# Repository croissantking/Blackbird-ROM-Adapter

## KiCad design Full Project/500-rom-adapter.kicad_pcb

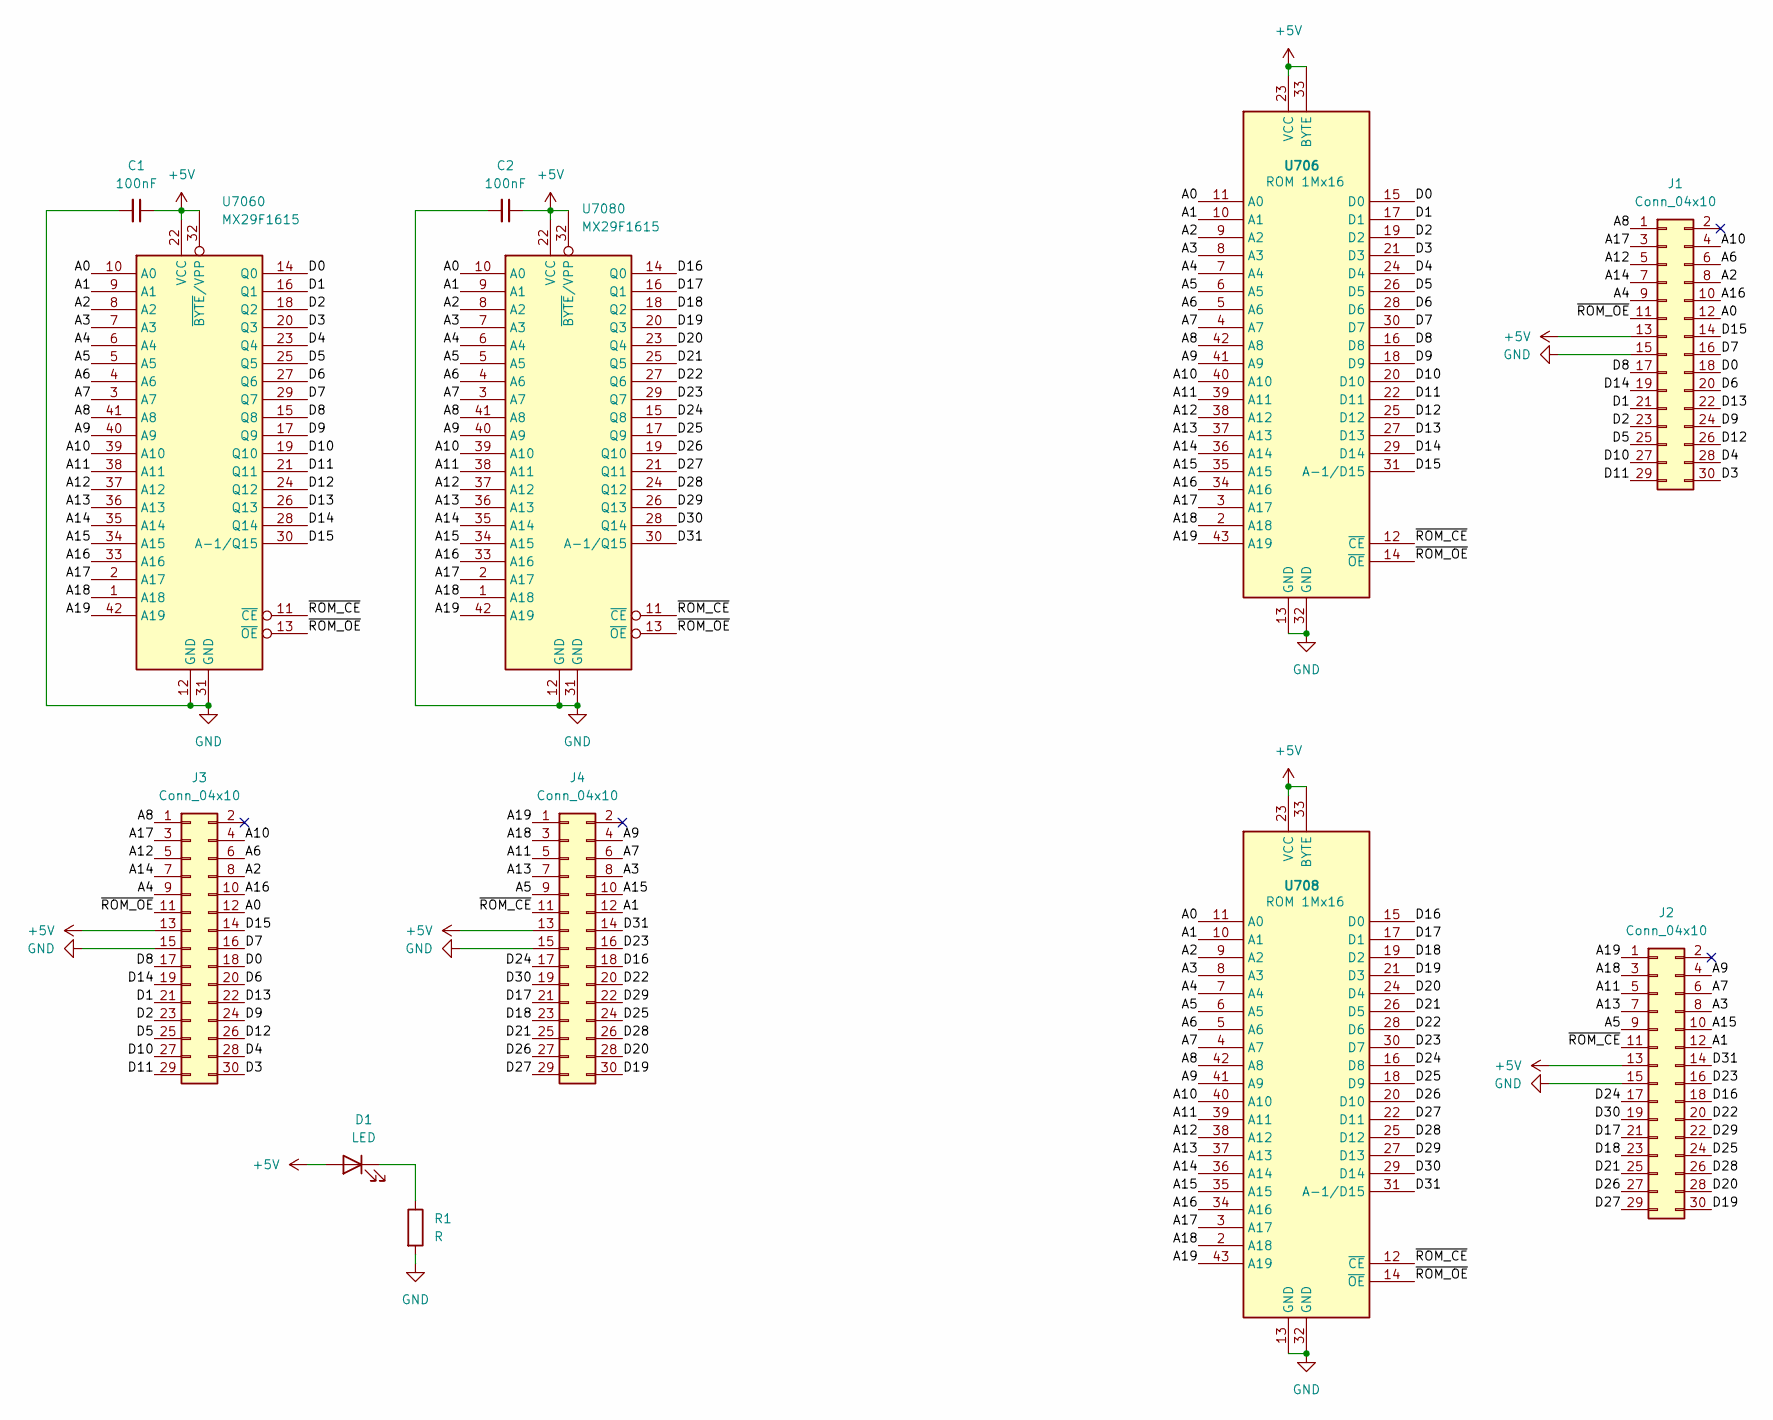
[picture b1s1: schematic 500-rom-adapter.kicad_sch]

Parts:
C1, C2: 100nF; C_0805_2012Metric_Pad1.18x1.45mm_HandSolder
D1: LED; LED_0805_2012Metric
J1, J2, J3, J4: Conn_04x10; PinSocket_3x10_P2.00mm_Vertical_PB500
R1: R; R_0805_2012Metric_Pad1.20x1.40mm_HandSolder
U706, U708: ROM 1Mx16; SOP-44_12.6_CASTELLATED
U7060, U7080: MX29F1615; DIP-42_W15.24mm_Socket_LongPads

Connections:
+5V: C1.1, C2.1, D1.2 (A), J1.13, J2.13, J3.13, J4.13, U706.23 (VCC), U706.33 (BYTE), U708.23 (VCC), U708.33 (BYTE), U7060.22 (VCC), U7060.32 (~BYTE/VPP), U7080.22 (VCC), U7080.32 (~BYTE/VPP); also elsewhere on the board
/A0: J1.12, J3.12, U706.11 (A0), U708.11 (A0), U7060.10 (A0), U7080.10 (A0)
/A1: J2.12, J4.12, U706.10 (A1), U708.10 (A1), U7060.9 (A1), U7080.9 (A1)
/A2: J1.8, J3.8, U706.9 (A2), U708.9 (A2), U7060.8 (A2), U7080.8 (A2)
/A3: J2.8, J4.8, U706.8 (A3), U708.8 (A3), U7060.7 (A3), U7080.7 (A3)
/A4: J1.9, J3.9, U706.7 (A4), U708.7 (A4), U7060.6 (A4), U7080.6 (A4)
/A5: J2.9, J4.9, U706.6 (A5), U708.6 (A5), U7060.5 (A5), U7080.5 (A5)
/A6: J1.6, J3.6, U706.5 (A6), U708.5 (A6), U7060.4 (A6), U7080.4 (A6)
/A7: J2.6, J4.6, U706.4 (A7), U708.4 (A7), U7060.3 (A7), U7080.3 (A7)
/A8: J1.1, J3.1, U706.42 (A8), U708.42 (A8), U7060.41 (A8), U7080.41 (A8)
/A9: J2.4, J4.4, U706.41 (A9), U708.41 (A9), U7060.40 (A9), U7080.40 (A9)
/A10: J1.4, J3.4, U706.40 (A10), U708.40 (A10), U7060.39 (A10), U7080.39 (A10)
/A11: J2.5, J4.5, U706.39 (A11), U708.39 (A11), U7060.38 (A11), U7080.38 (A11)
/A12: J1.5, J3.5, U706.38 (A12), U708.38 (A12), U7060.37 (A12), U7080.37 (A12)
/A13: J2.7, J4.7, U706.37 (A13), U708.37 (A13), U7060.36 (A13), U7080.36 (A13)
/A14: J1.7, J3.7, U706.36 (A14), U708.36 (A14), U7060.35 (A14), U7080.35 (A14)
/A15: J2.10, J4.10, U706.35 (A15), U708.35 (A15), U7060.34 (A15), U7080.34 (A15)
/A16: J1.10, J3.10, U706.34 (A16), U708.34 (A16), U7060.33 (A16), U7080.33 (A16)
/A17: J1.3, J3.3, U706.3 (A17), U708.3 (A17), U7060.2 (A17), U7080.2 (A17)
/A18: J2.3, J4.3, U706.2 (A18), U708.2 (A18), U7060.1 (A18), U7080.1 (A18)
/A19: J2.1, J4.1, U706.43 (A19), U708.43 (A19), U7060.42 (A19), U7080.42 (A19)
/D0: J1.18, J3.18, U706.15 (D0), U7060.14 (Q0)
/D1: J1.21, J3.21, U706.17 (D1), U7060.16 (Q1)
/D2: J1.23, J3.23, U706.19 (D2), U7060.18 (Q2)
/D3: J1.30, J3.30, U706.21 (D3), U7060.20 (Q3)
/D4: J1.28, J3.28, U706.24 (D4), U7060.23 (Q4)
/D5: J1.25, J3.25, U706.26 (D5), U7060.25 (Q5)
/D6: J1.20, J3.20, U706.28 (D6), U7060.27 (Q6)
/D7: J1.16, J3.16, U706.30 (D7), U7060.29 (Q7)
/D8: J1.17, J3.17, U706.16 (D8), U7060.15 (Q8)
/D9: J1.24, J3.24, U706.18 (D9), U7060.17 (Q9)
/D10: J1.27, J3.27, U706.20 (D10), U7060.19 (Q10)
/D11: J1.29, J3.29, U706.22 (D11), U7060.21 (Q11)
/D12: J1.26, J3.26, U706.25 (D12), U7060.24 (Q12)
/D13: J1.22, J3.22, U706.27 (D13), U7060.26 (Q13)
/D14: J1.19, J3.19, U706.29 (D14), U7060.28 (Q14)
/D15: J1.14, J3.14, U706.31 (A-1/D15), U7060.30 (A-1/Q15)
/D16: J2.18, J4.18, U708.15 (D0), U7080.14 (Q0)
/D17: J2.21, J4.21, U708.17 (D1), U7080.16 (Q1)
/D18: J2.23, J4.23, U708.19 (D2), U7080.18 (Q2)
/D19: J2.30, J4.30, U708.21 (D3), U7080.20 (Q3)
/D20: J2.28, J4.28, U708.24 (D4), U7080.23 (Q4)
/D21: J2.25, J4.25, U708.26 (D5), U7080.25 (Q5)
/D22: J2.20, J4.20, U708.28 (D6), U7080.27 (Q6)
/D23: J2.16, J4.16, U708.30 (D7), U7080.29 (Q7)
/D24: J2.17, J4.17, U708.16 (D8), U7080.15 (Q8)
/D25: J2.24, J4.24, U708.18 (D9), U7080.17 (Q9)
/D26: J2.27, J4.27, U708.20 (D10), U7080.19 (Q10)
/D27: J2.29, J4.29, U708.22 (D11), U7080.21 (Q11)
/D28: J2.26, J4.26, U708.25 (D12), U7080.24 (Q12)
/D29: J2.22, J4.22, U708.27 (D13), U7080.26 (Q13)
/D30: J2.19, J4.19, U708.29 (D14), U7080.28 (Q14)
/D31: J2.14, J4.14, U708.31 (A-1/D15), U7080.30 (A-1/Q15)
/~ROM_CE: J2.11, J4.11, U706.12 (~CE), U708.12 (~CE), U7060.11 (~CE), U7080.11 (~CE)
/~ROM_OE: J1.11, J3.11, U706.14 (~OE), U708.14 (~OE), U7060.13 (~OE), U7080.13 (~OE)
GND: C1.2, C2.2, J1.15, J2.15, J3.15, J4.15, R1.2, U706.13 (GND), U706.32 (GND), U708.13 (GND), U708.32 (GND), U7060.12 (GND), U7060.31 (GND), U7080.12 (GND), U7080.31 (GND)
unnamed 56: D1.1 (K), R1.1; also elsewhere on the board

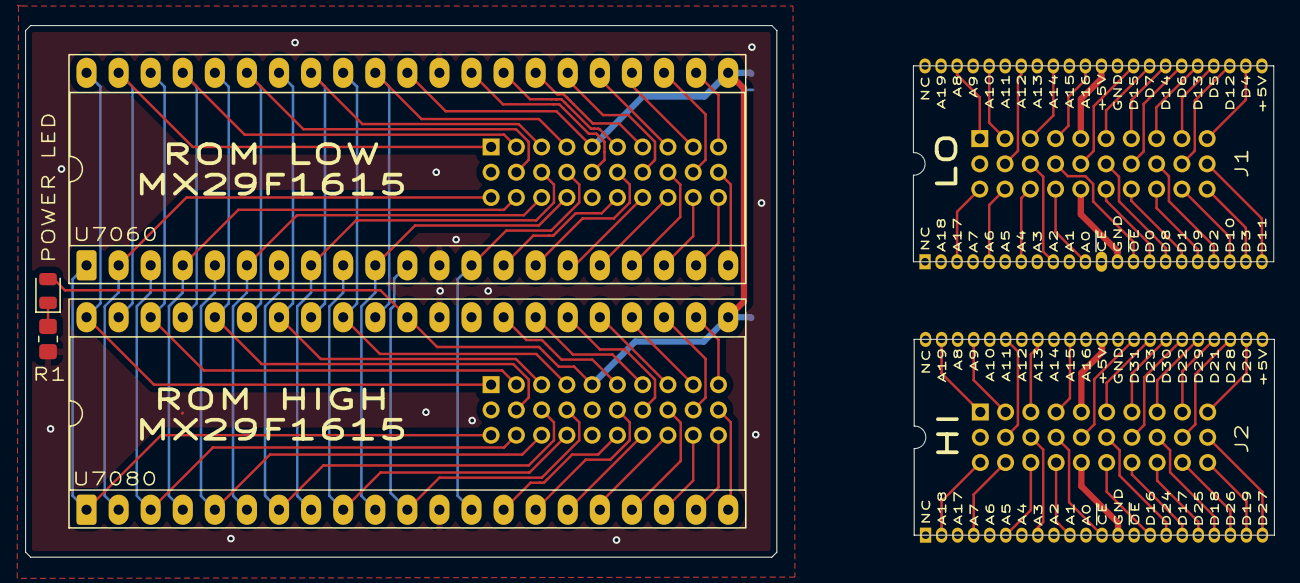
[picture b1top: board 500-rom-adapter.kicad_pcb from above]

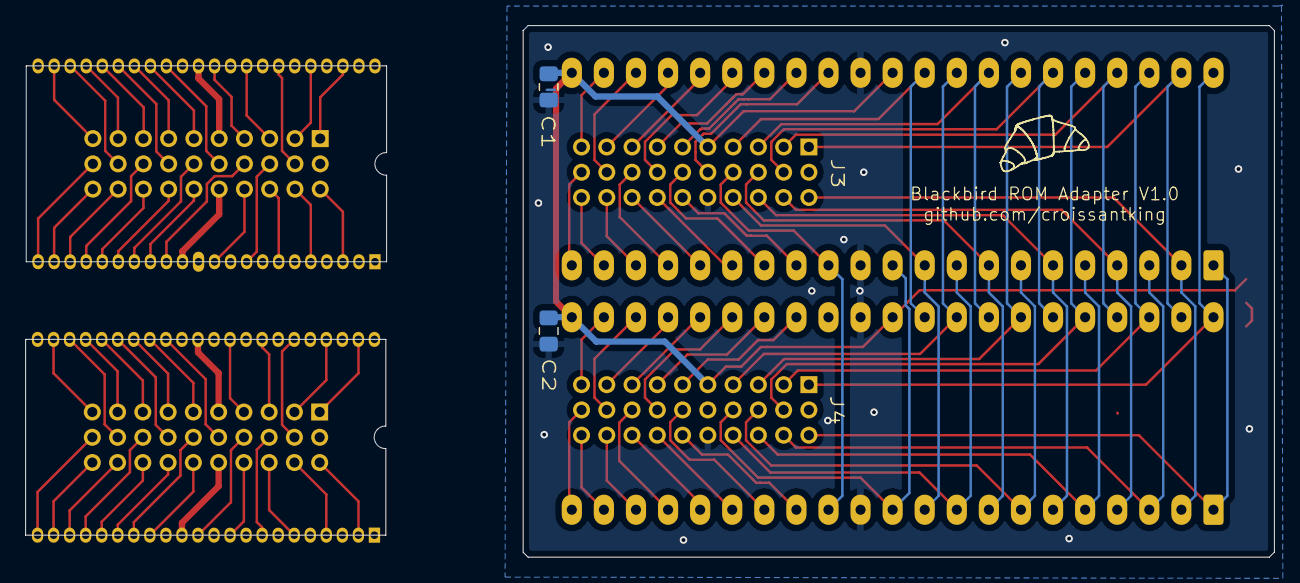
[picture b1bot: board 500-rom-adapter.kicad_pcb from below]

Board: 2 copper layers, 98.9 x 42.1 mm, 12 parts (2 on the bottom side), 57 nets.

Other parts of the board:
POWER LED: LED; LED_0805_2012Metric

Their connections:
+5V: POWER LED.2 (A); also elsewhere on the board
unnamed 56: POWER LED.1 (K); also elsewhere on the board

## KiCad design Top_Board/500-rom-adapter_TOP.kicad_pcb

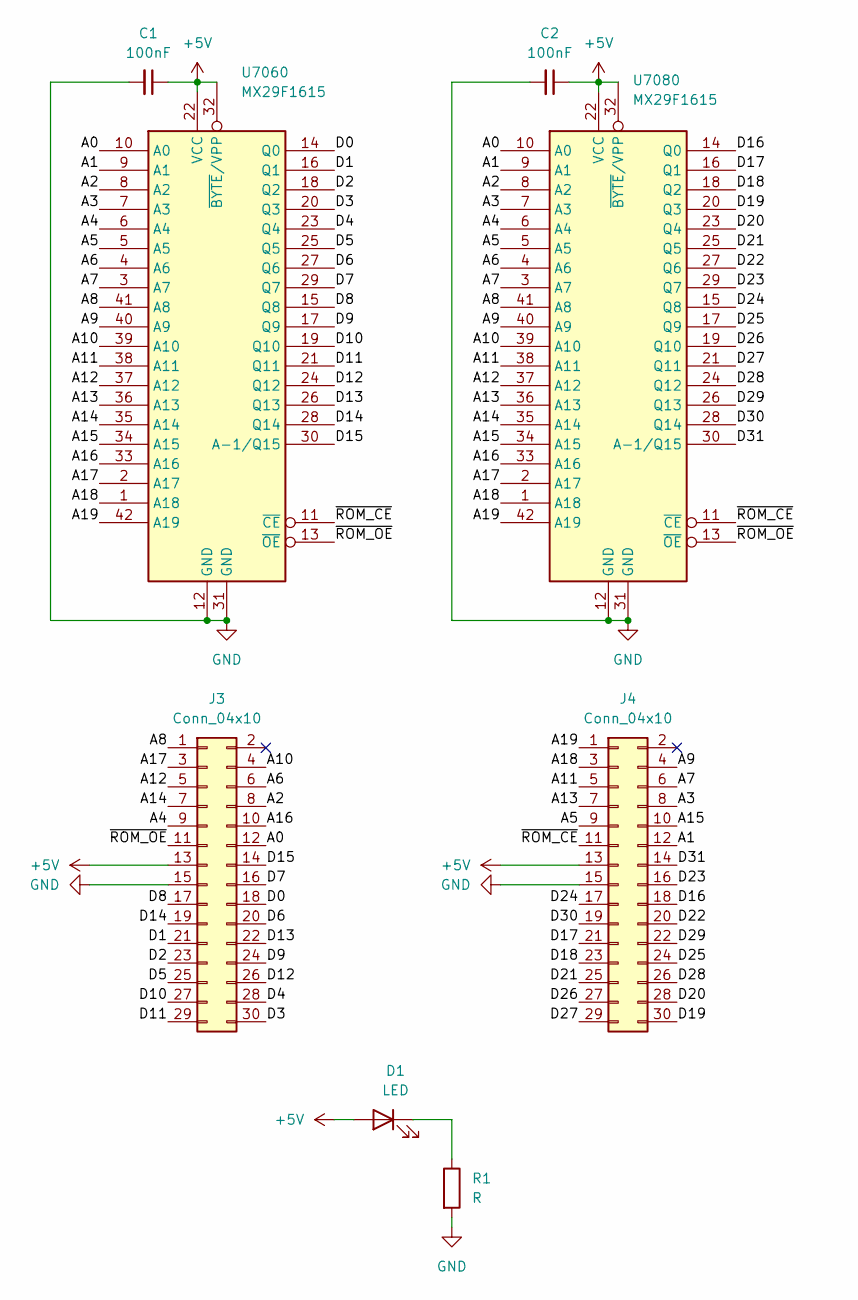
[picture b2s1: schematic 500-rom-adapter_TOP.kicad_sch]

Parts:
C1, C2: 100nF; C_0805_2012Metric_Pad1.18x1.45mm_HandSolder
D1: LED; LED_0805_2012Metric
J3, J4: Conn_04x10; PinSocket_3x10_P2.00mm_Vertical_PB500
R1: R; R_0805_2012Metric_Pad1.20x1.40mm_HandSolder
U7060, U7080: MX29F1615; DIP-42_W15.24mm_Socket_LongPads

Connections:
+5V: C1.1, C2.1, D1.2 (A), J3.13, J4.13, U7060.22 (VCC), U7060.32 (~BYTE/VPP), U7080.22 (VCC), U7080.32 (~BYTE/VPP)
/A0: J3.12, U7060.10 (A0), U7080.10 (A0)
/A1: J4.12, U7060.9 (A1), U7080.9 (A1)
/A2: J3.8, U7060.8 (A2), U7080.8 (A2)
/A3: J4.8, U7060.7 (A3), U7080.7 (A3)
/A4: J3.9, U7060.6 (A4), U7080.6 (A4)
/A5: J4.9, U7060.5 (A5), U7080.5 (A5)
/A6: J3.6, U7060.4 (A6), U7080.4 (A6)
/A7: J4.6, U7060.3 (A7), U7080.3 (A7)
/A8: J3.1, U7060.41 (A8), U7080.41 (A8)
/A9: J4.4, U7060.40 (A9), U7080.40 (A9)
/A10: J3.4, U7060.39 (A10), U7080.39 (A10)
/A11: J4.5, U7060.38 (A11), U7080.38 (A11)
/A12: J3.5, U7060.37 (A12), U7080.37 (A12)
/A13: J4.7, U7060.36 (A13), U7080.36 (A13)
/A14: J3.7, U7060.35 (A14), U7080.35 (A14)
/A15: J4.10, U7060.34 (A15), U7080.34 (A15)
/A16: J3.10, U7060.33 (A16), U7080.33 (A16)
/A17: J3.3, U7060.2 (A17), U7080.2 (A17)
/A18: J4.3, U7060.1 (A18), U7080.1 (A18)
/A19: J4.1, U7060.42 (A19), U7080.42 (A19)
/D0: J3.18, U7060.14 (Q0)
/D1: J3.21, U7060.16 (Q1)
/D2: J3.23, U7060.18 (Q2)
/D3: J3.30, U7060.20 (Q3)
/D4: J3.28, U7060.23 (Q4)
/D5: J3.25, U7060.25 (Q5)
/D6: J3.20, U7060.27 (Q6)
/D7: J3.16, U7060.29 (Q7)
/D8: J3.17, U7060.15 (Q8)
/D9: J3.24, U7060.17 (Q9)
/D10: J3.27, U7060.19 (Q10)
/D11: J3.29, U7060.21 (Q11)
/D12: J3.26, U7060.24 (Q12)
/D13: J3.22, U7060.26 (Q13)
/D14: J3.19, U7060.28 (Q14)
/D15: J3.14, U7060.30 (A-1/Q15)
/D16: J4.18, U7080.14 (Q0)
/D17: J4.21, U7080.16 (Q1)
/D18: J4.23, U7080.18 (Q2)
/D19: J4.30, U7080.20 (Q3)
/D20: J4.28, U7080.23 (Q4)
/D21: J4.25, U7080.25 (Q5)
/D22: J4.20, U7080.27 (Q6)
/D23: J4.16, U7080.29 (Q7)
/D24: J4.17, U7080.15 (Q8)
/D25: J4.24, U7080.17 (Q9)
/D26: J4.27, U7080.19 (Q10)
/D27: J4.29, U7080.21 (Q11)
/D28: J4.26, U7080.24 (Q12)
/D29: J4.22, U7080.26 (Q13)
/D30: J4.19, U7080.28 (Q14)
/D31: J4.14, U7080.30 (A-1/Q15)
/~ROM_CE: J4.11, U7060.11 (~CE), U7080.11 (~CE)
/~ROM_OE: J3.11, U7060.13 (~OE), U7080.13 (~OE)
GND: C1.2, C2.2, J3.15, J4.15, R1.2, U7060.12 (GND), U7060.31 (GND), U7080.12 (GND), U7080.31 (GND)
unnamed: D1.1 (K), R1.1

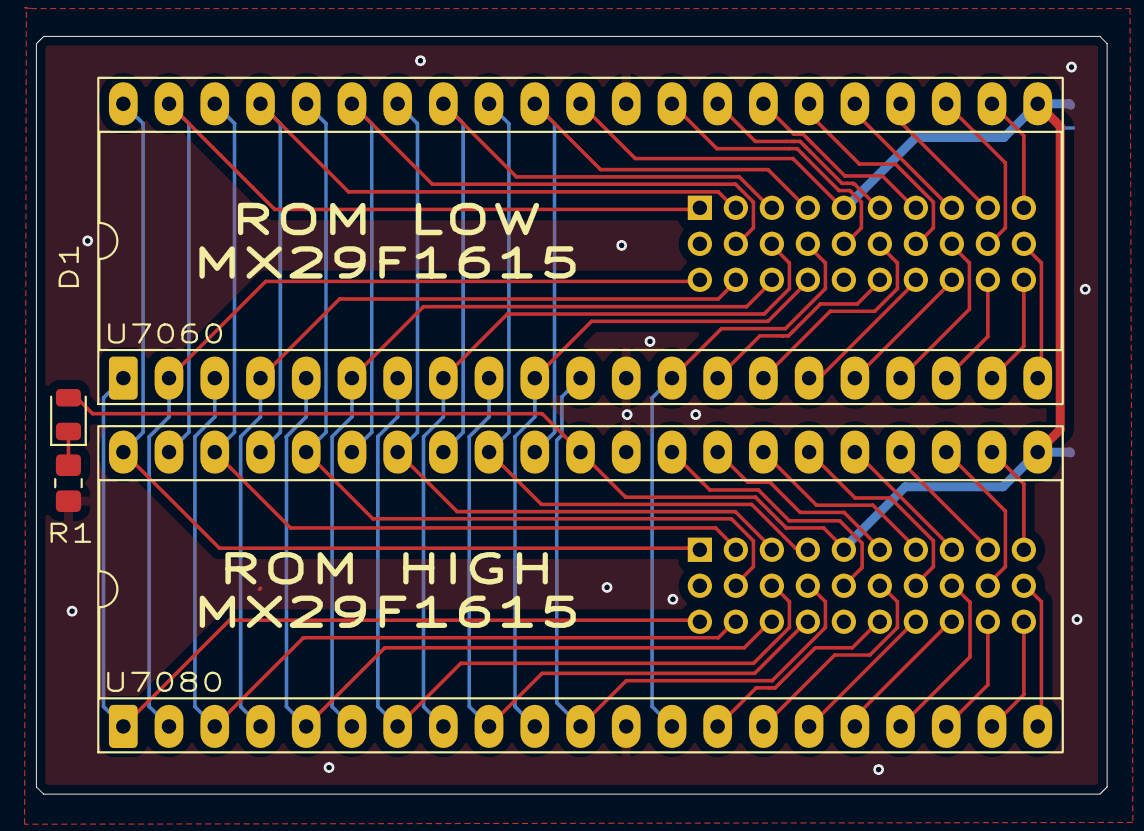
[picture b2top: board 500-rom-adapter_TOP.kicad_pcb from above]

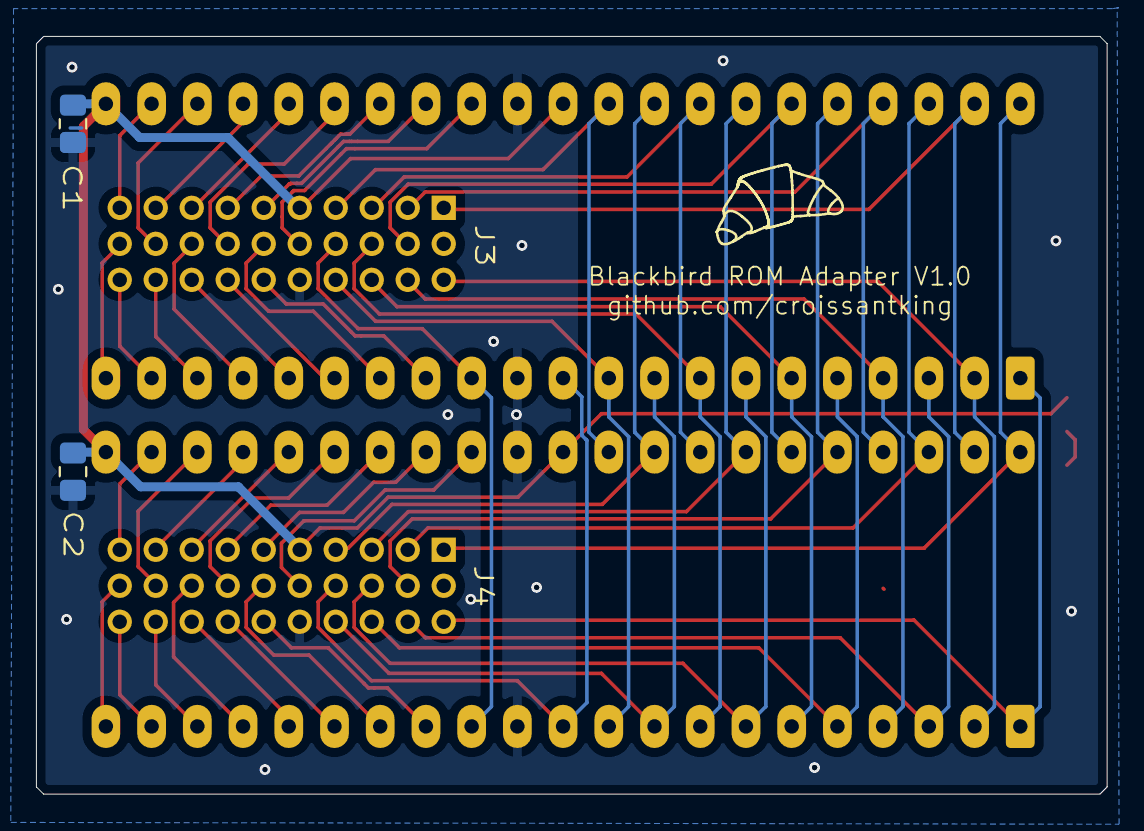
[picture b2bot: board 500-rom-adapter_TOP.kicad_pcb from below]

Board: 2 copper layers, 59.5 x 42.1 mm, 8 parts (2 on the bottom side), 57 nets.
